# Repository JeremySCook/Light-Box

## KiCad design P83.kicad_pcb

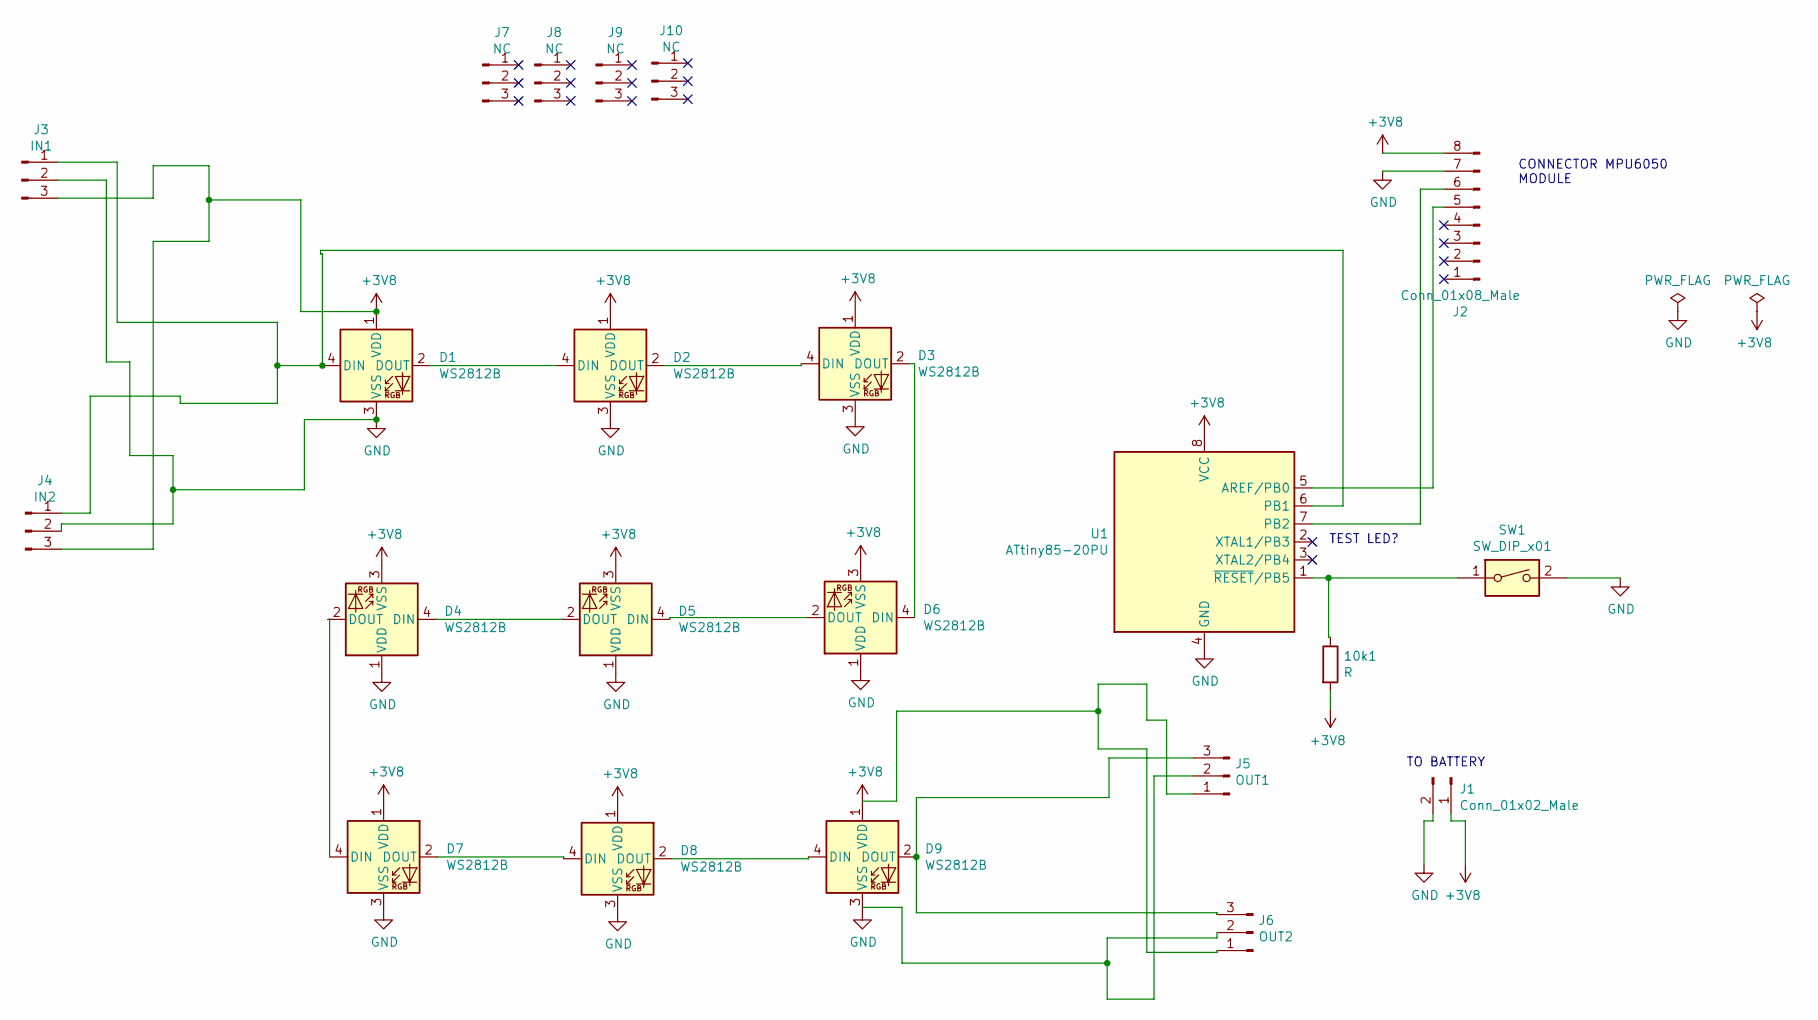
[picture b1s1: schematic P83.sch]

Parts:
10k1: R; R_0805_2012Metric
D1, D2, D3, D4, D5, D6, D7, D8, D9: WS2812B; LED_WS2812B_PLCC4_5.0x5.0mm_P3.2mm
J1: Conn_01x02_Male; PinHeader_1x02_P2.54mm_Horizontal
J2: Conn_01x08_Male; PinHeader_1x08_P2.54mm_Vertical
J3: IN1; PinHeader_1x03_P2.54mm_Vertical
J4: IN2; PinHeader_1x03_P2.54mm_Vertical
J5: OUT1; PinHeader_1x03_P2.54mm_Vertical
J6: OUT2; PinHeader_1x03_P2.54mm_Vertical
J7, J8, J9, J10: NC; PinHeader_1x03_P2.54mm_Vertical
SW1: SW_DIP_x01; SW_DIP_SPSTx01_Piano_10.8x4.1mm_W7.62mm_P2.54mm
U1: ATtiny85-20PU; DIP-8_W7.62mm

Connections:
+3V8: 10k1.2, D1.1 (VDD), D2.1 (VDD), D3.1 (VDD), D4.3 (VSS), D5.3 (VSS), D6.3 (VSS), D7.1 (VDD), D8.1 (VDD), D9.1 (VDD), J1.1, J2.8, J3.3, J4.3, U1.8 (VCC)
GND: D1.3 (VSS), D2.3 (VSS), D3.3 (VSS), D4.1 (VDD), D5.1 (VDD), D6.1 (VDD), D7.3 (VSS), D8.3 (VSS), D9.3 (VSS), J1.2, J2.7, J3.2, J4.2, SW1.2, U1.4 (GND)
unnamed: 10k1.1, SW1.1, U1.1 (~RESET~/PB5)
unnamed: D1.2 (DOUT), D2.4 (DIN)
unnamed: D1.4 (DIN), J3.1, J4.1, U1.6 (PB1)
unnamed: D2.2 (DOUT), D3.4 (DIN)
unnamed: D3.2 (DOUT), D6.4 (DIN)
unnamed: D4.2 (DOUT), D7.4 (DIN)
unnamed: D4.4 (DIN), D5.2 (DOUT)
unnamed: D5.4 (DIN), D6.2 (DOUT)
unnamed: D7.2 (DOUT), D8.4 (DIN)
unnamed: D8.2 (DOUT), D9.4 (DIN)
unnamed: D9.2 (DOUT), J5.3, J6.3
unnamed: J2.5, U1.5 (AREF/PB0)
unnamed: J2.6, U1.7 (PB2)
unnamed: J5.1, J6.1
unnamed: J5.2, J6.2

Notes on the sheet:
TO BATTERY
CONNECTOR MPU6050 MODULE
TEST LED?

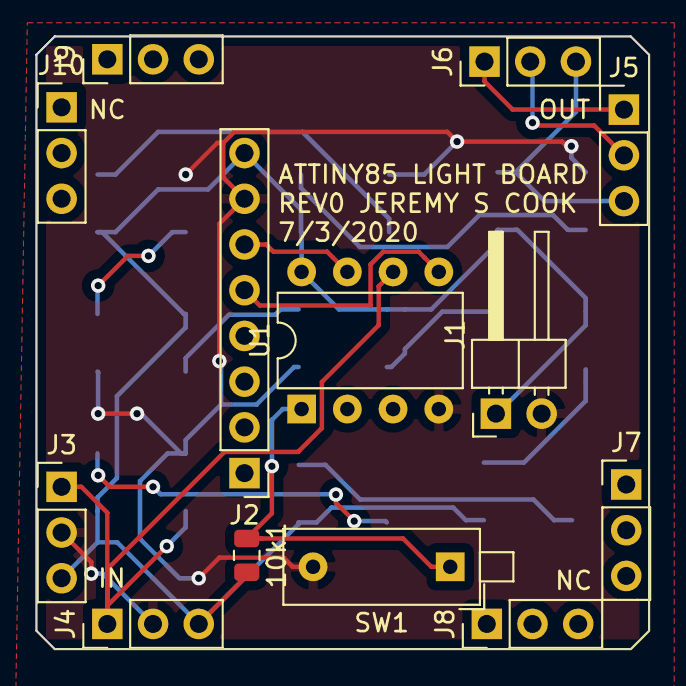
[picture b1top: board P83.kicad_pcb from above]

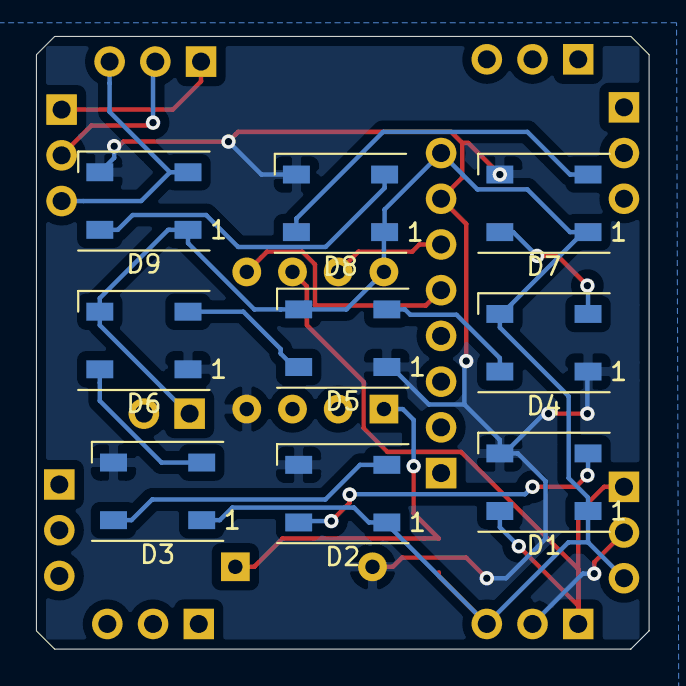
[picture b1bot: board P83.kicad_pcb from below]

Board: 2 copper layers, 34.0 x 34.0 mm, 22 parts (9 on the bottom side), 17 nets.
